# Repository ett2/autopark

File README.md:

# AutoPark
Repo for the embedded portion of AutoPark senior design project

Includes: 
- Lots of testing modules as keepsakes
- Fob
- Sensors
- State Driver
- Screen testing

Part of this project was developed for a course called ENGI 301. All relevant files to that class are in the ENGI 301 folder.
For further information about that portion of the project, go to:
https://www.hackster.io/eunice-tan/remote-controlled-lighting-system-b601c9

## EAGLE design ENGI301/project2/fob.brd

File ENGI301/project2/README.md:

# ENGI 301 Project 2 Documentation

I developed a PCB design for the fob portion of the AutoPark project, which is designed to be a first-iteration test of the components in a PCB.
This was also designed as a part of the ENGI 301 Project 2.

Included in this directory:
- Schematic file
- Board file
- Parts library
- Bill of Materials
- Gerber files
- Pictures of the PCB design

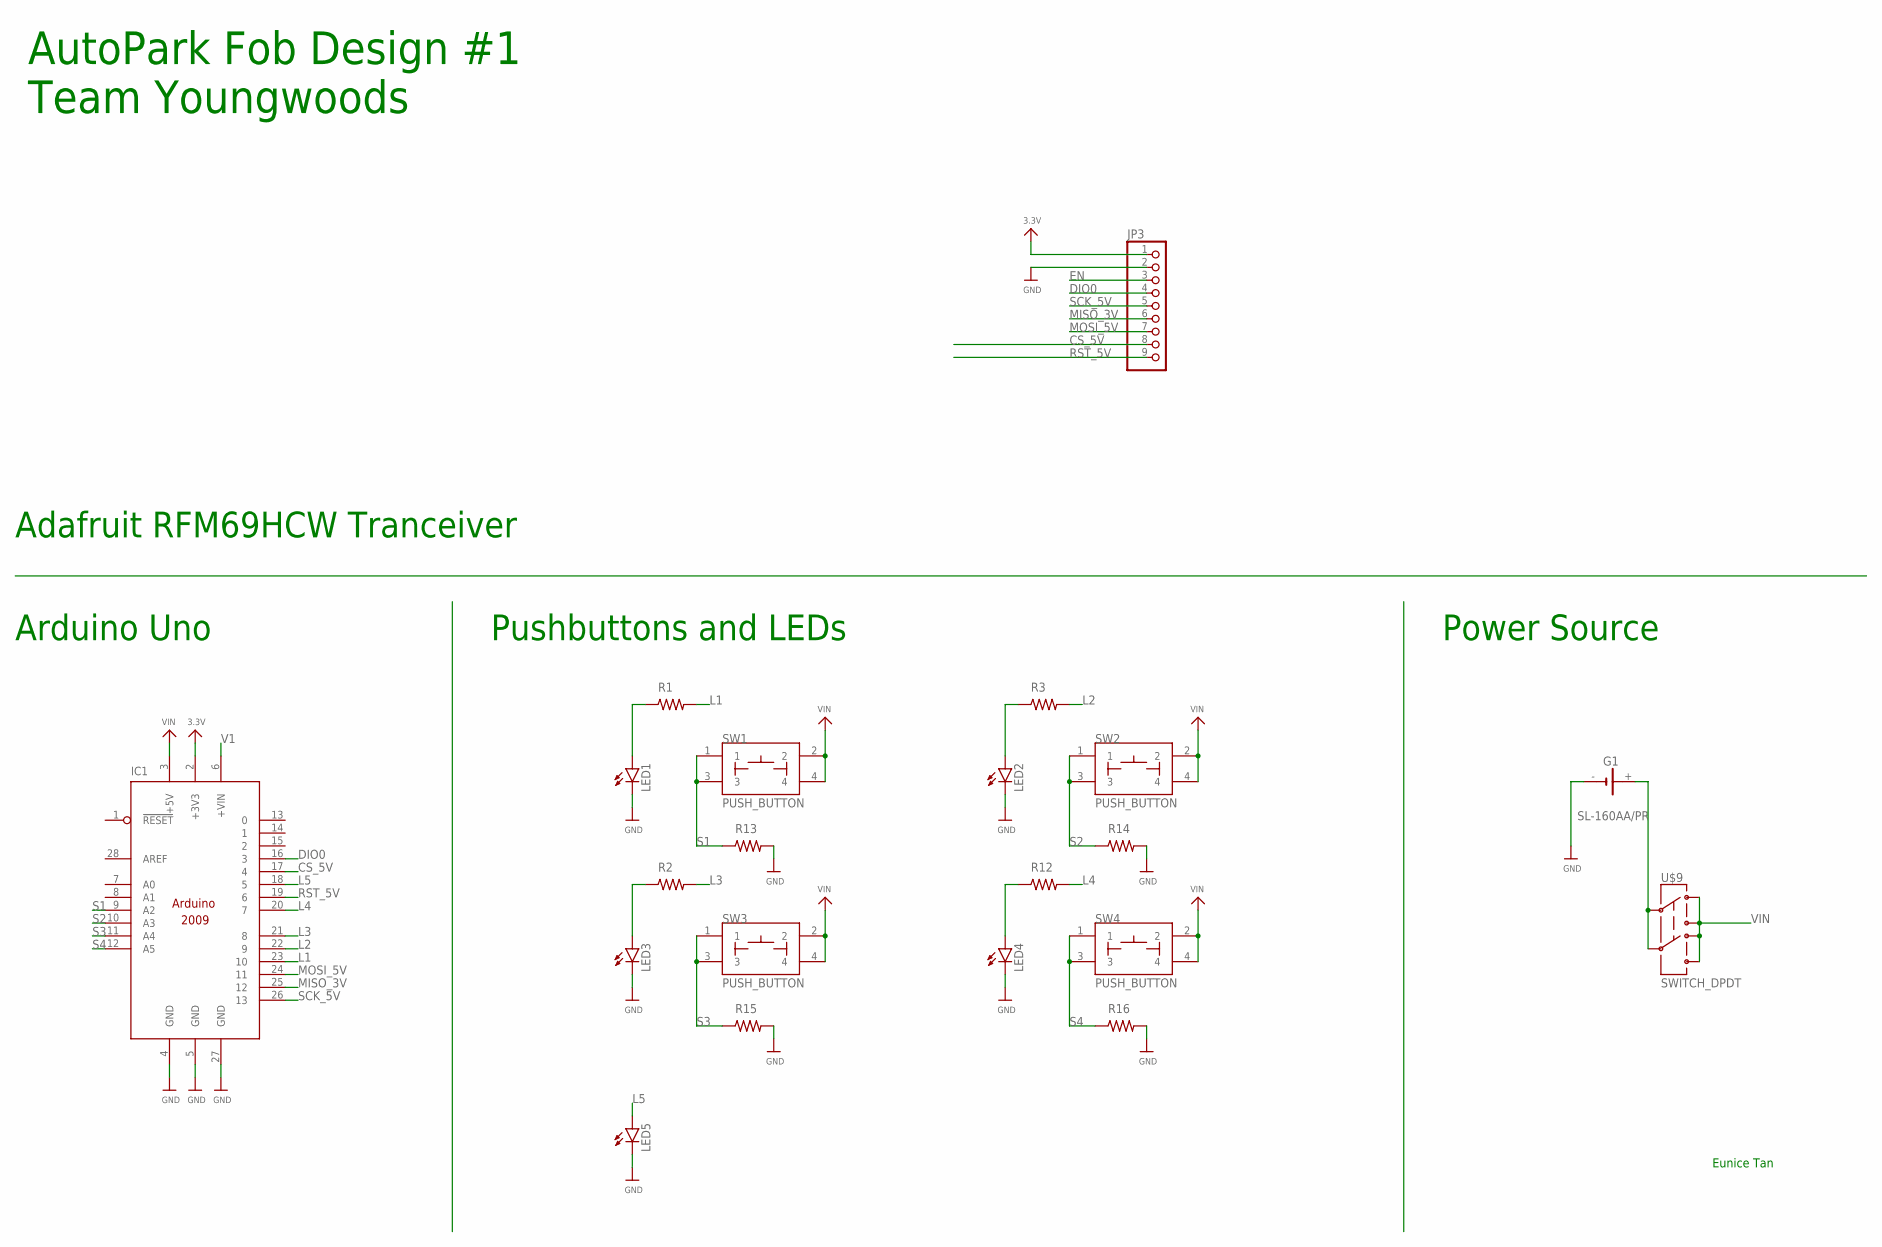
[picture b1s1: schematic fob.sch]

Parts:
G1: SL-160AA/PR
IC1: ARDUINO2009_10; ARDUINO2009
JP3: HEADER-1X970MIL; 1X09_ROUND_70
LED1, LED2, LED3, LED4, LED5: LED5MM
R1, R2, R3, R12, R13, R14, R15, R16: R_R0805; R0805
SW1, SW2, SW3, SW4: PUSH_BUTTON; BUTTON_12.5MM
U$9: SWITCH_DPDT; JS_DPDT_TH

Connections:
3.3V: IC1.2 (+3V3), JP3.1
CS_5V: IC1.17 (4), JP3.8
DIO0: IC1.16 (3), JP3.4
EN: JP3.3
GND: G1.-, IC1.4 (GND), IC1.5 (GND), IC1.27 (GND), JP3.2, LED1.K (C), LED2.K (C), LED3.K (C), LED4.K (C), LED5.K (C), R13.2, R14.2, R15.2, R16.2
L1: IC1.23 (10), R1.2
L2: IC1.22 (9), R3.2
L3: IC1.21 (8), R2.2
L4: IC1.20 (7), R12.2
L5: IC1.18 (5), LED5.A
MISO_3V: IC1.25 (12), JP3.6
MOSI_5V: IC1.24 (11), JP3.7
unnamed: G1.+, U$9.2, U$9.5
unnamed: LED1.A, R1.1
unnamed: LED3.A, R2.1
unnamed: LED2.A, R3.1
unnamed: LED4.A, R12.1
RST_5V: IC1.19 (6), JP3.9
S1: IC1.9 (A2), R13.1, SW1.1, SW1.3
S2: IC1.10 (A3), R14.1, SW2.1, SW2.3
S3: IC1.11 (A4), R15.1, SW3.1, SW3.3
S4: IC1.12 (A5), R16.1, SW4.1, SW4.3
SCK_5V: IC1.26 (13), JP3.5
V1: IC1.6 (+VIN)
VIN: IC1.3 (+5V), SW1.2, SW1.4, SW2.2, SW2.4, SW3.2, SW3.4, SW4.2, SW4.4, U$9.1, U$9.3, U$9.4, U$9.6

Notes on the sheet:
Adafruit RFM69HCW Tranceiver
Arduino Uno
Pushbuttons and LEDs
Power Source
Eunice Tan
AutoPark Fob Design #1 Team Youngwoods

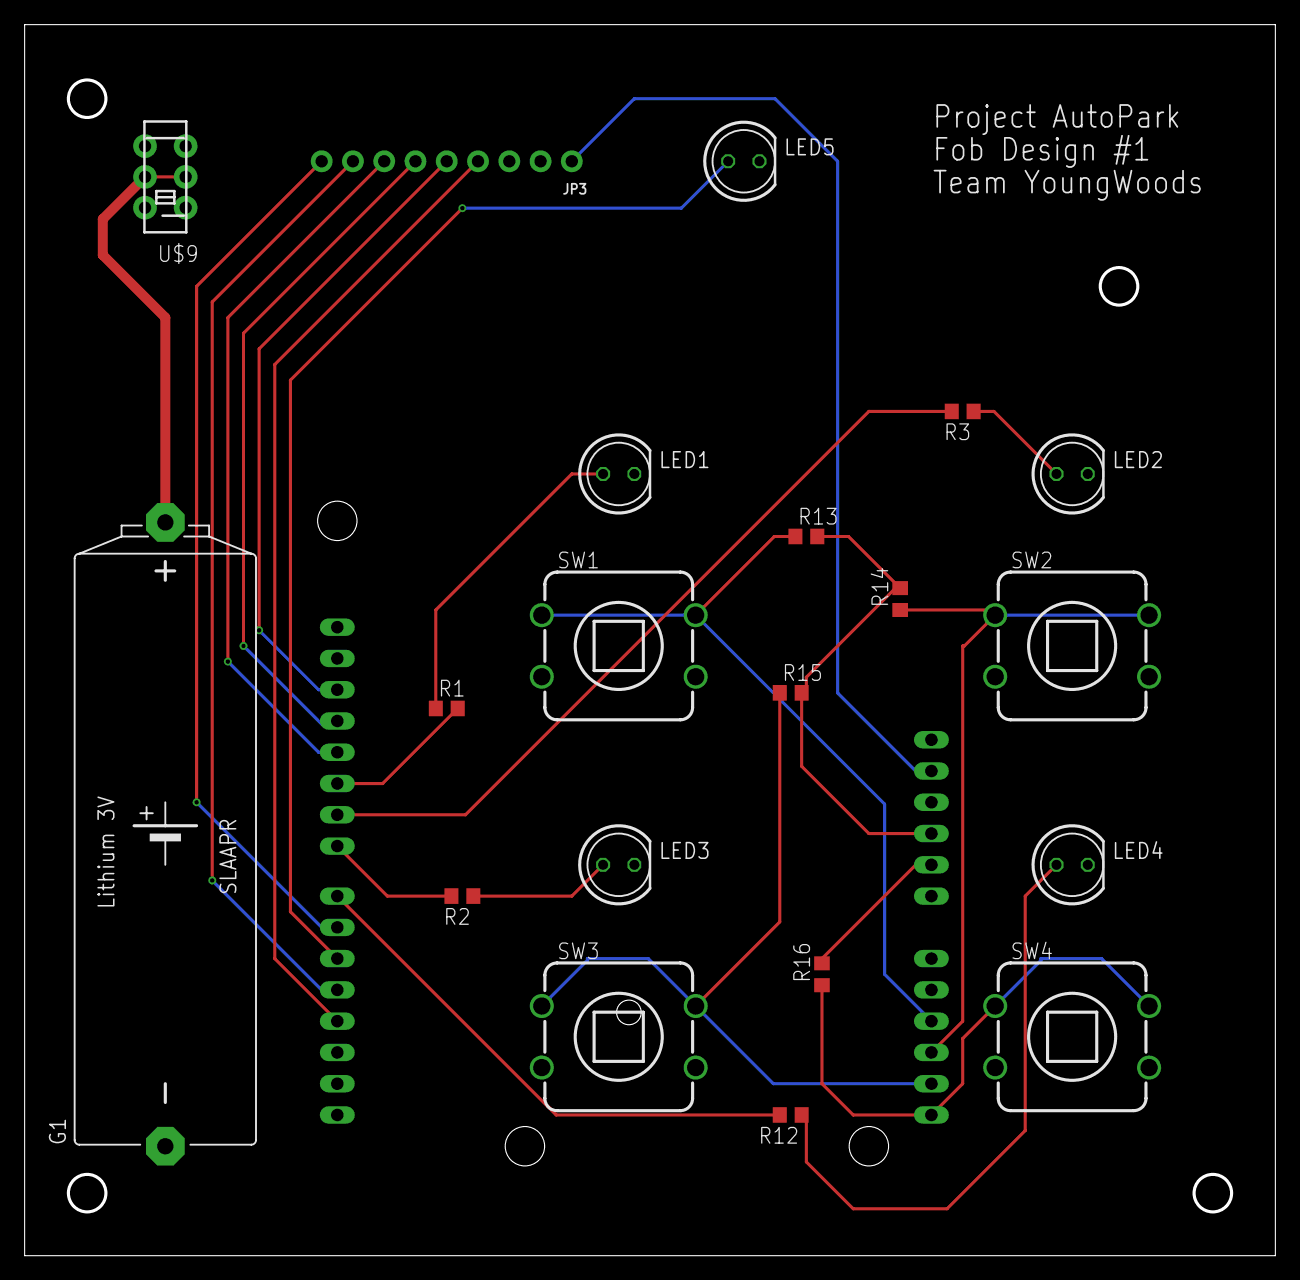
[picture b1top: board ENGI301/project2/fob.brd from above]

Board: 4 copper layers, 101.6 x 100.0 mm, 21 parts (1 on the bottom side), 23 nets.

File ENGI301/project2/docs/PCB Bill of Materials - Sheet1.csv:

Part Name,Designator,Manufacturer/MPN,Quanitity,Description
Arduino Uno,Arduino 2009,Arduino,1,Microcontroller board
6-pin Switch,SWITCH_DPDT,Various manufacturers,1,Found in FEP: no need to order
5mm LED ,"LED1, LED2, LED3, LED4, LED5",Various manufacturers,5,Found in OEDK and FEP: no need to order
RFM69HCW Radio Module,JP3,Adafruit,1,Radio transceiver/receiver module
Tactile Push Buttons,"SW1, SW2, SW3, SW4",Various manufacturers,4,Found in OEDK: no need to order
100-ohm resistor,"R1, R2, R3, R12, R13, R14, R15, R16",Various manufacturers,8,Found in FEP: no need to order
Through-hole power source connector,G1,N/A,1,Can connect to various power sources depending on need

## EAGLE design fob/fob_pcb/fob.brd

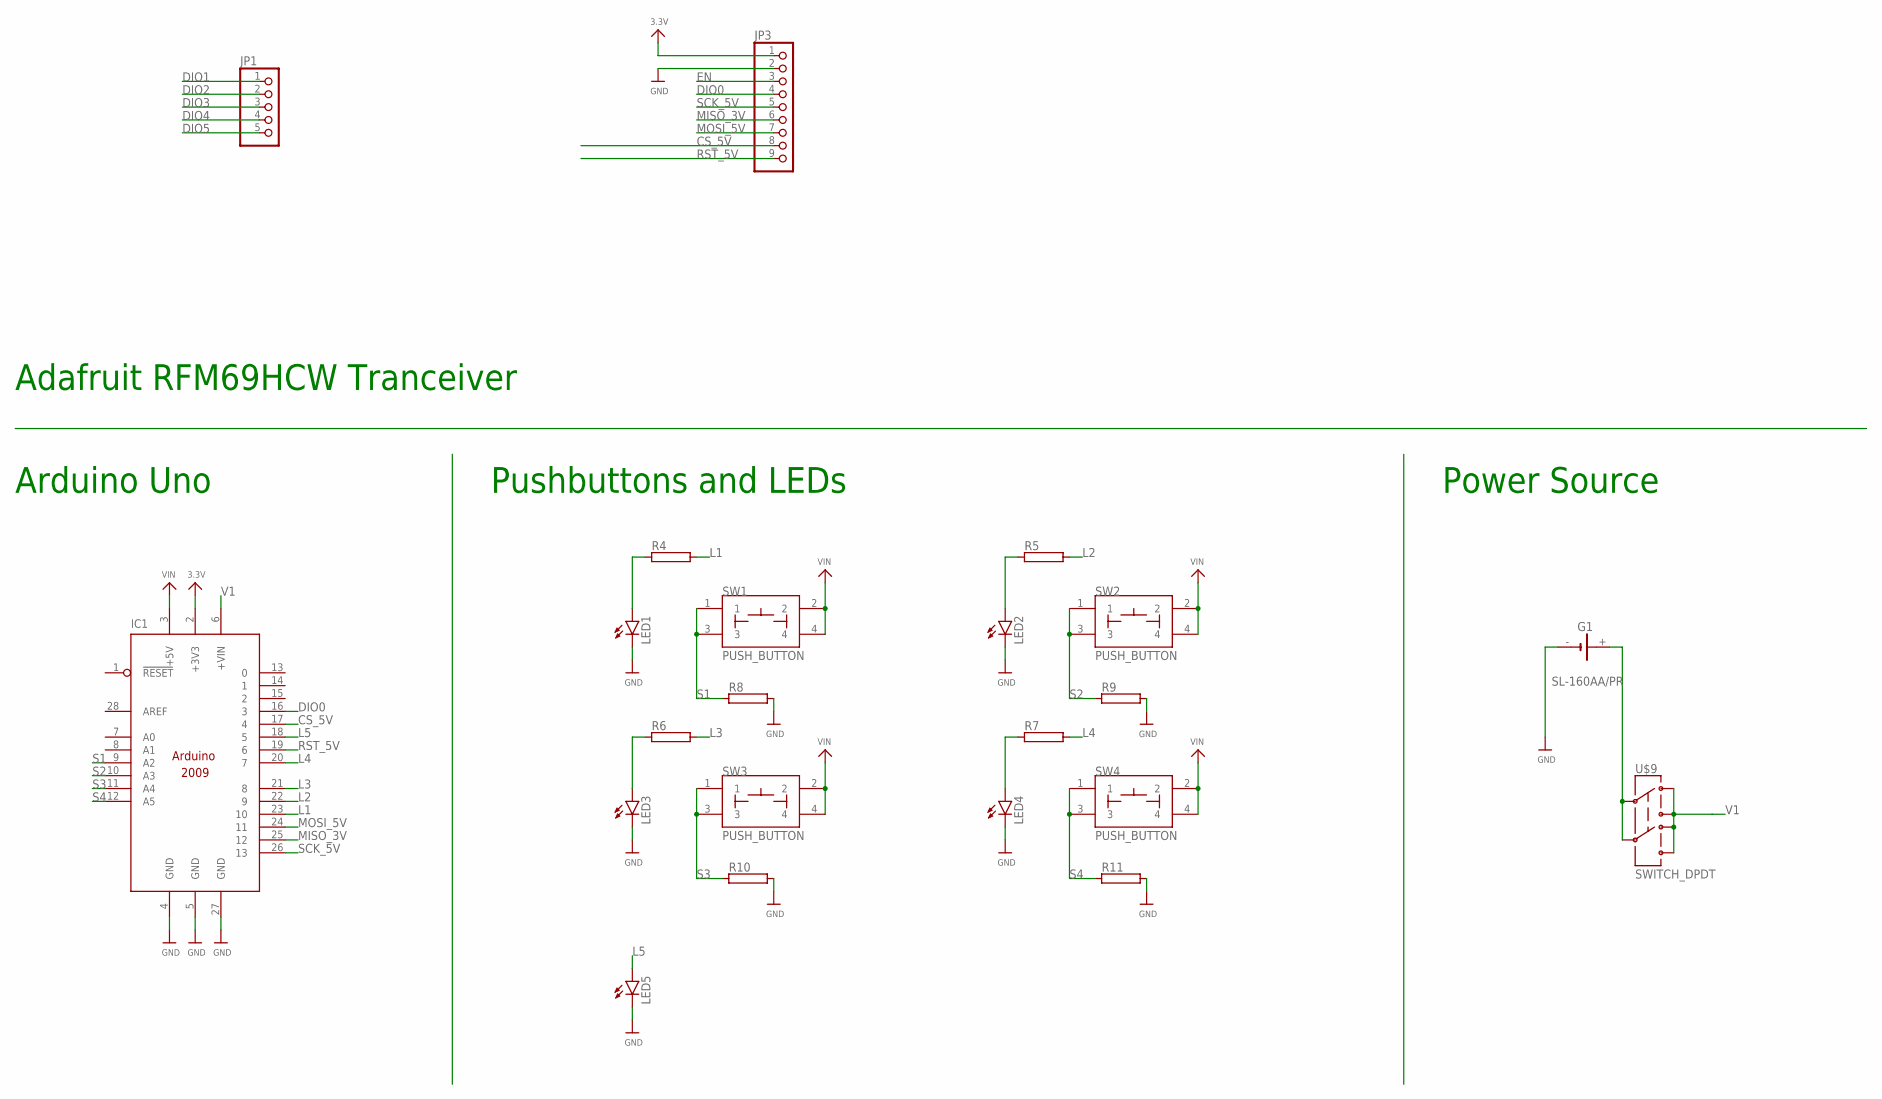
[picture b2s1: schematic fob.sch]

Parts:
G1: SL-160AA/PR
IC1: ARDUINO2009_10; ARDUINO2009
JP1: HEADER-1X570MIL; 1X05_ROUND_70
JP3: HEADER-1X970MIL; 1X09_ROUND_70
LED1, LED2, LED3, LED4, LED5: LED5MM
R4, R5, R6, R7, R8, R9, R10, R11: RAC01; AC01
SW1, SW2, SW3, SW4: PUSH_BUTTON; BUTTON_12.5MM
U$9: SWITCH_DPDT; JS_DPDT_TH

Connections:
3.3V: IC1.2 (+3V3), JP3.1
CS_5V: IC1.17 (4), JP3.8
DIO0: IC1.16 (3), JP3.4
DIO1: JP1.1
DIO2: JP1.2
DIO3: JP1.3
DIO4: JP1.4
DIO5: JP1.5
EN: JP3.3
GND: G1.-, IC1.4 (GND), IC1.5 (GND), IC1.27 (GND), JP3.2, LED1.K (C), LED2.K (C), LED3.K (C), LED4.K (C), LED5.K (C), R8.2, R9.2, R10.2, R11.2
L1: IC1.23 (10), R4.2
L2: IC1.22 (9), R5.2
L3: IC1.21 (8), R6.2
L4: IC1.20 (7), R7.2
L5: IC1.18 (5), LED5.A
MISO_3V: IC1.25 (12), JP3.6
MOSI_5V: IC1.24 (11), JP3.7
unnamed: G1.+, U$9.2, U$9.5
unnamed: LED1.A, R4.1
unnamed: LED3.A, R6.1
unnamed: LED2.A, R5.1
unnamed: LED4.A, R7.1
RST_5V: IC1.19 (6), JP3.9
S1: IC1.9 (A2), R8.1, SW1.1, SW1.3
S2: IC1.10 (A3), R9.1, SW2.1, SW2.3
S3: IC1.11 (A4), R10.1, SW3.1, SW3.3
S4: IC1.12 (A5), R11.1, SW4.1, SW4.3
SCK_5V: IC1.26 (13), JP3.5
V1: IC1.6 (+VIN), U$9.1, U$9.3, U$9.4, U$9.6
VIN: IC1.3 (+5V), SW1.2, SW1.4, SW2.2, SW2.4, SW3.2, SW3.4, SW4.2, SW4.4

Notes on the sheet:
Adafruit RFM69HCW Tranceiver
Arduino Uno
Pushbuttons and LEDs
Power Source

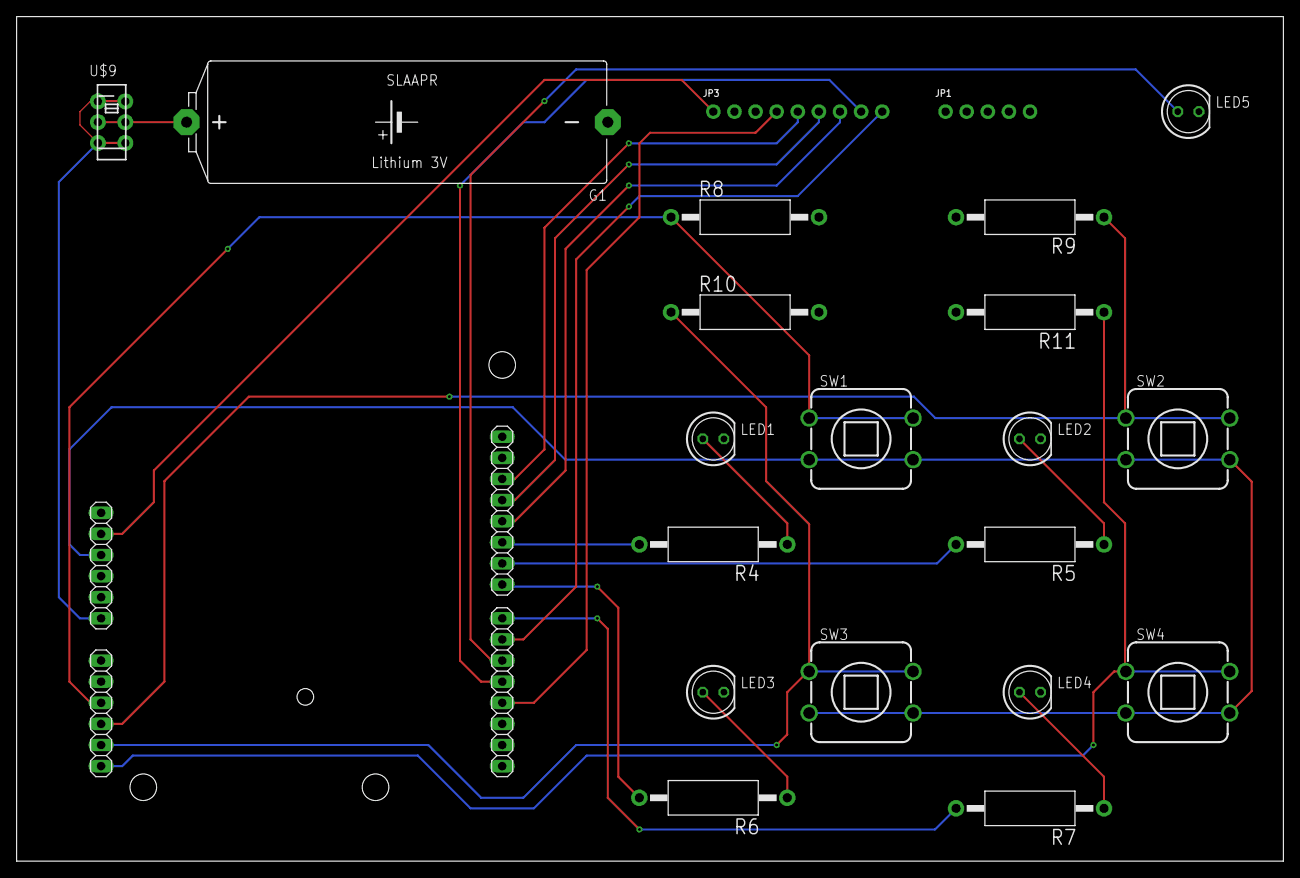
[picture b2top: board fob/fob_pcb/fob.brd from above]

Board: 2 copper layers, 152.4 x 101.6 mm, 22 parts (0 on the bottom side), 24 nets.

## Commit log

2022-10-26 Added test files for fob interface
2022-11-02 Folder Organization :)
    put things in places that they belong
2022-11-02 Add updated fob system
2022-11-07 Second iteration of tests
    Full working model (mvp) finished :)
2022-11-07 Working model + tests
    - Finished working model (mvp)
    - Added a few versions of test files
2022-11-28 clean up + new files
    - organized files better
    - added emergency braking stuff
    - added state change output stuff
2022-11-30 added pcb design 1 for fob
    includes brd and sch files
2022-11-30 Update fob.brd
    yep
2022-12-04 added gerber files for iteration 1
2022-12-05 add statechange files
2022-12-05 updated statechange.py
2022-12-12 added files for engi301 project 1
    wooo
2022-12-12 added lots of documentation
    ENGI 301 final project stuff
2022-12-12 project 2 stuff
    asdlkjdaskljkljasd
2022-12-12 added pcb documentation
2022-12-13 added to PCB design
    - mounting holes
    - documentation
    - titles and stuff
2022-12-13 Added gbr files
2022-12-13 updated fob brd picture

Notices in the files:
parts and their libraries:
microbuilder: This work is placed in the public domain, and may be freely used for commercial and non-commercial work with the following conditions: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
